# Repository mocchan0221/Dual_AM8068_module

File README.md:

# Dual_AM8068_module

## What is this？
AMtekの激安HブリッジモータドライバAM8068を２つ利用した２つのDCモーター、または１つのステッピングモーターを駆動できるモジュール

### 特徴
- コンパクト
    - 横幅300milなのでブレッドボードやICソケットで利用可能
- パスコン実装済み
    - 電源ラインに0.1μF(100nF)と100μF、各出力ラインに0.1μF積層セラコンを配置済み
- 使いやすいピン配置
    - 電源ラインや入出力のピンをまとめて配置

### 仕様

|パラメータ|記号|Min|Max|単位|
|--|--|--|--|--|
|電源電圧|VCC|2|6.8|V|
|入力電圧|Vin|-0.3|VCC+0.3|V|
|出力電流|Imax|0|0.9|A|
|PWM入力周波数|Fin|0.02|65|kHz|

### ファイル
回路図、PCBファイルのPDFデータは[doc](/doc)に、KiCADファイルは[src](/src/)にあります

## License

このデバイスのライセンスは CERN-OHL-Sです\
ライセンスの詳細は [LICENSE](LICENSE) をご覧ください

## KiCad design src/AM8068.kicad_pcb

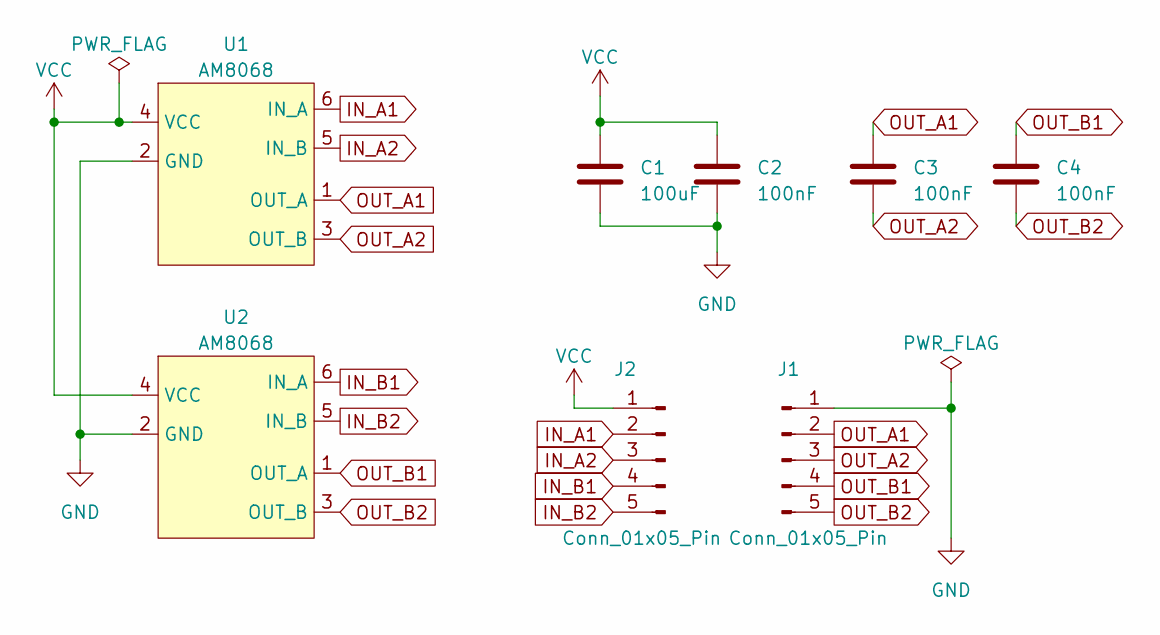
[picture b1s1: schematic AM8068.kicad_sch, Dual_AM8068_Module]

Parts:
C1: 100uF; C_1206_3216Metric
C2, C3, C4: 100nF; C_0603_1608Metric
J1, J2: Conn_01x05_Pin; NTH5
U1, U2: AM8068; SOT-23-6

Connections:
GND: C1.2, C2.2, J1.1, U1.2 (GND), U2.2 (GND)
IN_A1: J2.2, U1.6 (IN_A)
IN_A2: J2.3, U1.5 (IN_B)
IN_B1: J2.4, U2.6 (IN_A)
IN_B2: J2.5, U2.5 (IN_B)
OUT_A1: C3.1, J1.2, U1.1 (OUT_A)
OUT_A2: C3.2, J1.3, U1.3 (OUT_B)
OUT_B1: C4.1, J1.4, U2.1 (OUT_A)
OUT_B2: C4.2, J1.5, U2.3 (OUT_B)
VCC: C1.1, C2.1, J2.1, U1.4 (VCC), U2.4 (VCC)

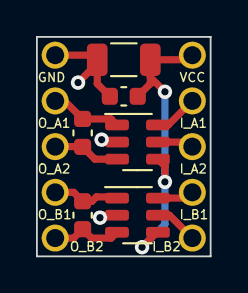
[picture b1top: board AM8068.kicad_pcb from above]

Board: 2 copper layers, 9.7 x 12.2 mm, 8 parts (0 on the bottom side), 10 nets.

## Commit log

2024-05-25 Create LICENSE
2024-05-25 add readme
2024-05-25 add files
2024-05-25 remove some files
2024-05-25 modify pcb file
2024-05-25 modify readme
2024-06-13 add pcb recomend
